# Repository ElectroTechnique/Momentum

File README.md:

# Momentum
Electrotechnique Momentum Synthesizer

3D Models - STL models of 3D printed components

Manual - User Manual including build guide

Momentum - Folder with source code, set-up for PlatformIO

SDCard - Folder with 'factory presets'. Copy the contents of the SDCard folder straight onto a formatted micro SD card

# Flashing firmware
Get the firmware hex file from [RELEASES](https://github.com/ElectroTechnique/Momentum/releases) on the right
See the User Manual sections on Flashing Firmware - use either TyUploader (recommended) or Teensy Loader.
TyUploader is in [TyTools Releases](https://github.com/Koromix/tytools/releases)
Teensy Loader is at [PJRC](https://www.pjrc.com/teensy/loader.html)

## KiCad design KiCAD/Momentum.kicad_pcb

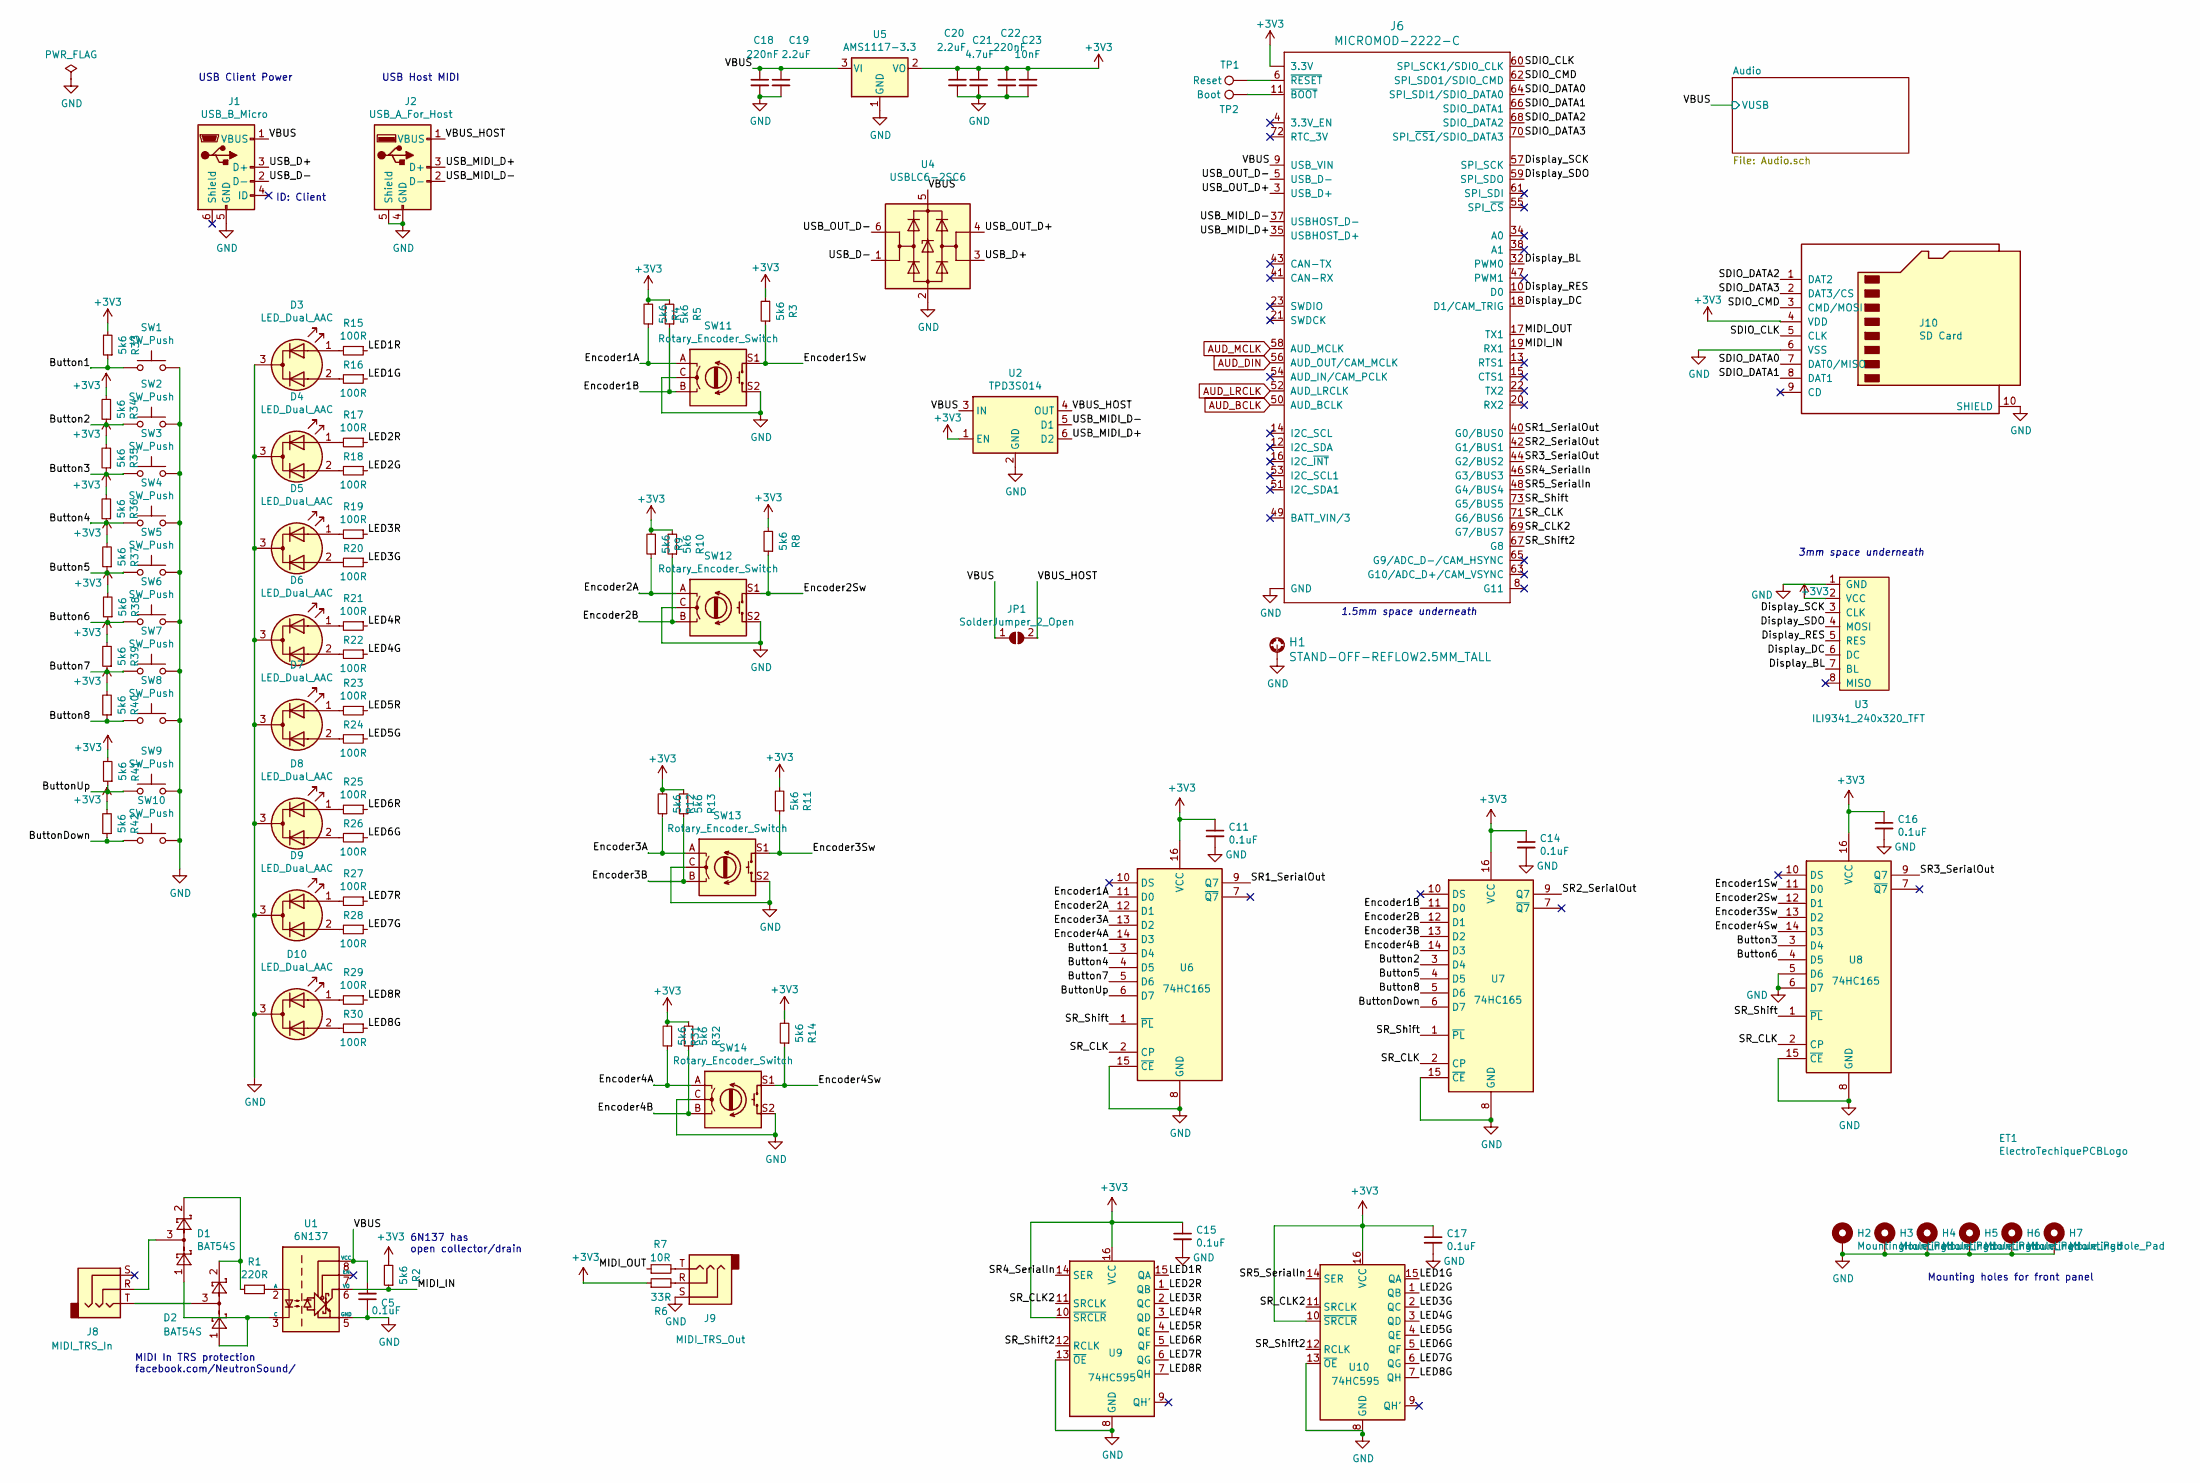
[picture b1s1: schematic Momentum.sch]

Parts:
C5, C11, C14, C15, C16, C17: 0.1uF; R_0805_2012Metric; LCSC C49678
C18, C22: 220nF; R_0805_2012Metric; LCSC C5378
C19, C20: 2.2uF; R_0805_2012Metric; LCSC C49217
C21: 4.7uF; R_0805_2012Metric; LCSC C1779
C23: 10nF; R_0805_2012Metric; LCSC C1710
D1, D2: BAT54S; SOT-23; LCSC C47546
D3, D4, D5, D6, D7, D8, D9, D10: LED_Dual_AAC; LED_D3.0mm-3
ET1: ElectroTechiquePCBLogo; ElectroTechniquePCBLogo
H1: STAND-OFF-REFLOW2.5MM_TALL; STAND-OFF-REFLOW-M2.5
H2, H3, H4, H5, H6, H7: MountingHole_Pad; MountingHole_3.2mm_M3_DIN965_Pad
J1: USB_B_Micro; USB_Micro-B_Molex_47346-0001; LCSC C132560
J2: USB_A_For_Host; USB_A_Stewart_SS-52100-001_Horizontal; LCSC C456008
J6: MICROMOD-2222-C; M.2-CONNECTOR-E; LCSC C841659
J8: MIDI_TRS_In; Jack_3.5mm_Ledino_KB3SPRS_Horizontal
J9: MIDI_TRS_Out; Jack_3.5mm_Ledino_KB3SPRS_Horizontal
J10: SD Card; MicroSD_Hroparts_TF-01A; LCSC C91145
JP1: SolderJumper_2_Open; SolderJumper-2_P1.3mm_Open_RoundedPad1.0x1.5mm
R1: 220R; R_0805_2012Metric; LCSC C17557
R2, R3, R4, R5, R8, R9, R10, R11, R12, R13, R14, R31, R32, R33, R34, R35, R36, R37, R38, R39, R40, R41, R42: 5k6; R_0805_2012Metric; LCSC C4382
R6: 33R; R_0805_2012Metric; LCSC C17634
R7: 10R; R_0805_2012Metric; LCSC C17415
R15, R16, R17, R18, R19, R20, R21, R22, R23, R24, R25, R26, R27, R28, R29, R30: 100R; R_0805_2012Metric; LCSC C17408
SW1, SW2, SW3, SW4, SW5, SW6, SW7, SW8, SW9, SW10: SW_Push; SW_PUSH-12mm
SW11, SW12, SW13, SW14: Rotary_Encoder_Switch; RotaryEncoder_Alps_EC11E-Switch_Vertical_H20mm
TP1: Reset; TestPoint_Pad_D1.5mm
TP2: Boot; TestPoint_Pad_D1.5mm
U1: 6N137; SMDIP-8_W9.53mm; LCSC C110020
U2: TPD3S014; SOT-23-6; LCSC C87384
U3: ILI9341_240x320_TFT; TFT-graphic_display_240x320_ILI9341
U4: USBLC6-2SC6; SOT-23-6; LCSC C7519
U5: AMS1117-3.3; SOT-223-3_TabPin2; LCSC C6186
U6, U7, U8: 74HC165; SOIC-16_3.9x9.9mm_P1.27mm; LCSC C5613
U9, U10: 74HC595; SOIC-16_3.9x9.9mm_P1.27mm; LCSC C5947

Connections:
+3V3: C11.1, C14.1, C15.1, C16.1, C17.1, C20.1, C21.1, C22.1, C23.1, J6.2 (3.3V), J6.74 (3.3V), J10.4 (VDD), R2.2, R3.2, R4.2, R5.2, R6.1, R8.2, R9.2, R10.2, R11.2, R12.2, R13.2, R14.2, R31.2, R32.2, R33.2, R34.2, R35.2, R36.2, R37.2, R38.2, R39.2, R40.2, R41.2, R42.2, U2.1 (EN), U3.2 (VCC), U5.2 (VO), U6.16 (VCC), U7.16 (VCC), U8.16 (VCC), U9.10 (~SRCLR), U9.16 (VCC), U10.10 (~SRCLR), U10.16 (VCC)
/Button1: R33.1, SW1.1, U6.3 (D4)
/Button2: R34.1, SW2.1, U7.3 (D4)
/Button3: R35.1, SW3.1, U8.3 (D4)
/Button4: R36.1, SW4.1, U6.4 (D5)
/Button5: R37.1, SW5.1, U7.4 (D5)
/Button6: R38.1, SW6.1, U8.4 (D5)
/Button7: R39.1, SW7.1, U6.5 (D6)
/Button8: R40.1, SW8.1, U7.5 (D6)
/ButtonDown: R42.1, SW10.1, U7.6 (D7)
/ButtonUp: R41.1, SW9.1, U6.6 (D7)
/Display_BL: J6.32 (PWM0), U3.7 (BL)
/Display_DC: J6.18 (D1/CAM_TRIG), U3.6 (DC)
/Display_RES: J6.10 (D0), U3.5 (RES)
/Display_SCK: J6.57 (SPI_SCK), U3.3 (CLK)
/Display_SDO: J6.59 (SPI_SDO), U3.4 (MOSI)
/Encoder1A: R4.1, SW11.A, U6.11 (D0)
/Encoder1B: R5.1, SW11.B, U7.11 (D0)
/Encoder1Sw: R3.1, SW11.S1, U8.11 (D0)
/Encoder2A: R9.1, SW12.A, U6.12 (D1)
/Encoder2B: R10.1, SW12.B, U7.12 (D1)
/Encoder2Sw: R8.1, SW12.S1, U8.12 (D1)
/Encoder3A: R12.1, SW13.A, U6.13 (D2)
/Encoder3B: R13.1, SW13.B, U7.13 (D2)
/Encoder3Sw: R11.1, SW13.S1, U8.13 (D2)
/Encoder4A: R31.1, SW14.A, U6.14 (D3)
/Encoder4B: R32.1, SW14.B, U7.14 (D3)
/Encoder4Sw: R14.1, SW14.S1, U8.14 (D3)
/LED1G: R16.1, U10.15 (QA)
/LED1R: R15.1, U9.15 (QA)
/LED2G: R18.1, U10.1 (QB)
/LED2R: R17.1, U9.1 (QB)
/LED3G: R20.1, U10.2 (QC)
/LED3R: R19.1, U9.2 (QC)
/LED4G: R22.1, U10.3 (QD)
/LED4R: R21.1, U9.3 (QD)
/LED5G: R24.1, U10.4 (QE)
/LED5R: R23.1, U9.4 (QE)
/LED6G: R26.1, U10.5 (QF)
/LED6R: R25.1, U9.5 (QF)
/LED7G: R28.1, U10.6 (QG)
/LED7R: R27.1, U9.6 (QG)
/LED8G: R30.1, U10.7 (QH)
/LED8R: R29.1, U9.7 (QH)
/MIDI_IN: J6.19 (RX1), R2.1, U1.6 (VO)
/MIDI_OUT: J6.17 (TX1), R7.1
/SDIO_CLK: J6.60 (SPI_SCK1/SDIO_CLK), J10.5 (CLK)
/SDIO_CMD: J6.62 (SPI_SDO1/SDIO_CMD), J10.3 (CMD/MOSI)
/SDIO_DATA0: J6.64 (SPI_SDI1/SDIO_DATA0), J10.7 (DAT0/MISO)
/SDIO_DATA1: J6.66 (SDIO_DATA1), J10.8 (DAT1)
/SDIO_DATA2: J6.68 (SDIO_DATA2), J10.1 (DAT2)
/SDIO_DATA3: J6.70 (SPI_~CS1~/SDIO_DATA3), J10.2 (DAT3/CS)
/SR1_SerialOut: J6.40 (G0/BUS0), U6.9 (Q7)
/SR2_SerialOut: J6.42 (G1/BUS1), U7.9 (Q7)
/SR3_SerialOut: J6.44 (G2/BUS2), U8.9 (Q7)
/SR4_SerialIn: J6.46 (G3/BUS3), U9.14 (SER)
/SR5_SerialIn: J6.48 (G4/BUS4), U10.14 (SER)
/SR_CLK: J6.71 (G6/BUS6), U6.2 (CP), U7.2 (CP), U8.2 (CP)
/SR_CLK2: J6.69 (G7/BUS7), U9.11 (SRCLK), U10.11 (SRCLK)
/SR_Shift: J6.73 (G5/BUS5), U6.1 (~PL), U7.1 (~PL), U8.1 (~PL)
/SR_Shift2: J6.67 (G8), U9.12 (RCLK), U10.12 (RCLK)
/USB_D+: J1.3 (D+), U4.3 (I/O2)
/USB_D-: J1.2 (D-), U4.1 (I/O1)
/USB_MIDI_D+: J2.3 (D+), J6.35 (USBHOST_D+), U2.6 (D2)
/USB_MIDI_D-: J2.2 (D-), J6.37 (USBHOST_D-), U2.5 (D1)
/USB_OUT_D+: J6.3 (USB_D+), U4.4 (I/O2)
/USB_OUT_D-: J6.5 (USB_D-), U4.6 (I/O1)
/VBUS: C5.2, C18.1, C19.1, J1.1 (VBUS), J6.9 (USB_VIN), JP1.1 (A), U1.8 (VCC), U2.3 (IN), U4.5 (VBUS), U5.3 (VI); also elsewhere on the board
/VBUS_HOST: J2.1 (VBUS), JP1.2 (B), U2.4 (OUT)
AUD_BCLK: J6.50 (AUD_BCLK); also elsewhere on the board
AUD_DIN: J6.56 (AUD_OUT/CAM_MCLK); also elsewhere on the board
AUD_LRCLK: J6.52 (AUD_LRCLK); also elsewhere on the board
AUD_MCLK: J6.58 (AUD_MCLK); also elsewhere on the board
GND: C5.1, C11.2, C14.2, C15.2, C16.2, C17.2, C18.2, C19.2, C20.2, C21.2, C22.2, C23.2, D3.3 (K), D4.3 (K), D5.3 (K), D6.3 (K), D7.3 (K), D8.3 (K), D9.3 (K), D10.3 (K), H1.1, H2.1, H3.1, H4.1, H5.1, H6.1, H7.1, J1.5 (GND), J2.4 (GND), J2.5 (Shield), J6.1 (GND), J6.7 (GND), J6.33 (GND), J6.36 (GND), J6.39 (GND), J6.45 (GND), J6.75 (GND), J9.S, J10.6 (VSS), J10.10 (SHIELD), SW1.2, SW2.2, SW3.2, SW4.2, SW5.2, SW6.2, SW7.2, SW8.2, SW9.2, SW10.2, SW11.C, SW11.S2, SW12.C, SW12.S2, SW13.C, SW13.S2, SW14.C, SW14.S2, U1.5 (GND), U2.2 (GND), U3.1 (GND), U4.2 (GND), U5.1 (GND), U6.8 (GND), U6.15 (~CE), U7.8 (GND), U7.15 (~CE), U8.5 (D6), U8.6 (D7), U8.8 (GND), U8.15 (~CE), U9.8 (GND), U9.13 (~OE), U10.8 (GND), U10.13 (~OE); also elsewhere on the board
unnamed: D1.1, D2.1, U1.3 (C)
unnamed: D1.2, D2.2, R1.2
unnamed: D1.3, J8.R
unnamed: D2.3, J8.T
unnamed: D3.1 (A1), R15.2
unnamed: D3.2 (A2), R16.2
unnamed: D4.1 (A1), R17.2
unnamed: D4.2 (A2), R18.2
unnamed: D5.1 (A1), R19.2
unnamed: D5.2 (A2), R20.2
unnamed: D6.1 (A1), R21.2
unnamed: D6.2 (A2), R22.2
unnamed: D7.1 (A1), R23.2
unnamed: D7.2 (A2), R24.2
unnamed: D8.1 (A1), R25.2
unnamed: D8.2 (A2), R26.2
unnamed: D9.1 (A1), R27.2
unnamed: D9.2 (A2), R28.2
unnamed: D10.1 (A1), R29.2
unnamed: D10.2 (A2), R30.2
unnamed: J6.6 (~RESET~), TP1.1
unnamed: J6.11 (~BOOT~), TP2.1
unnamed: J9.R, R6.2
unnamed: J9.T, R7.2
unnamed: R1.1, U1.2 (A)

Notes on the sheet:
USB Client Power
USB Host MIDI
MIDI In TRS protection facebook.com/NeutronSound/
ID: Client
1.5mm space underneath
3mm space underneath
Mounting holes for front panel
6N137 has open collector/drain

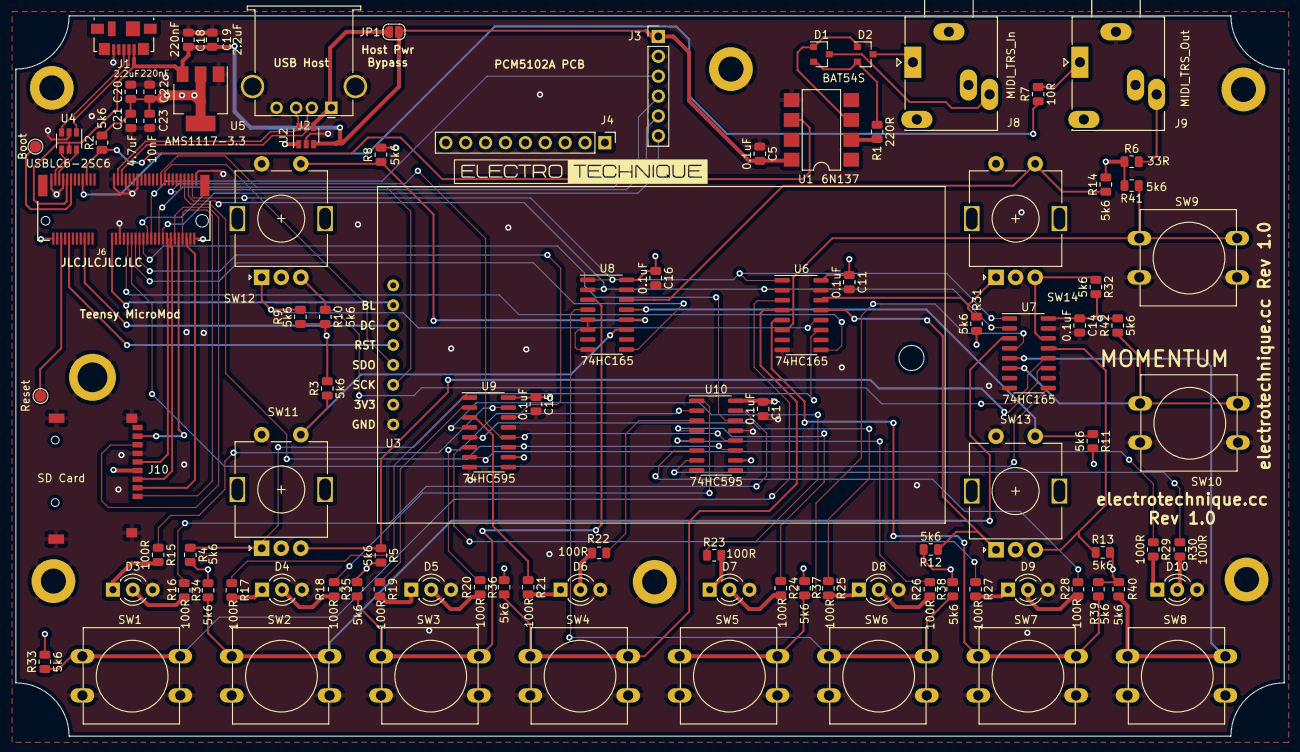
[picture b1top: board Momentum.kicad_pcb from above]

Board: 4 copper layers, 162.0 x 92.0 mm, 107 parts (0 on the bottom side), 99 nets.

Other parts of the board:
J3: PCM5102 PCB 1; PinHeader_1x06_P2.54mm_Vertical
J4: PCM5102 PCB 2; PinHeader_1x09_P2.54mm_Vertical

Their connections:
/VBUS: J3.1; also elsewhere on the board
AUD_BCLK: J3.5; also elsewhere on the board
AUD_DIN: J3.4; also elsewhere on the board
AUD_LRCLK: J3.3; also elsewhere on the board
AUD_MCLK: J3.6; also elsewhere on the board
GND: J3.2; also elsewhere on the board

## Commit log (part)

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2021-10-20 V1.0
2021-11-22 Based on TSynth V2.31
2022-12-18 Patch/Bank editing complete
2022-12-18 Settings working
2023-01-27 Patch saving, performance, defaults, key tracking and filter modulation.
2023-02-05 Add button held
2023-02-05 Performance, USB Host detect
2023-02-18 Sequencer working
2023-03-09 Arpeggiator working
2023-04-22 Fixes
2023-04-27 Sequencer
2023-04-27 Prevent button press causing rotation changes
2023-05-15 Two button press
2023-05-15 Keyboard
2023-07-10 Update LICENSE
2023-09-26 Issues 1,3,6,7,8 fixed
2023-10-09 V1.02 - Improve encoder acceleration
2023-10-09 V1.02 - Improve encoder acceleration - Issue 4
2023-10-09 Delete Firmware/Momentum_V1_02.hex
    Problem with low values
2023-12-25 V1.03 fix
2024-08-26 Exponential Envelope Fix from TSynth (Issue #140)
2024-08-26 Exp Envelope fix from TSynth (issue #140)
